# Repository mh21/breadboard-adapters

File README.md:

# breadboard-adapters

Various small schematics + PCBs for prototyping on breadboards

## TPS709xx breadboard adapter

TPS709xx breadboard adapter based on the reference design of the [TI datasheet](
http://www.ti.com/lit/ds/symlink/tps709.pdf).

2 layer board of 0.31x0.34 inches (7.77x8.66 mm). 

<a href="https://oshpark.com/shared_projects/ZPfzHzE1"></img></a>

Details: [TI datasheet](http://www.ti.com/lit/ds/symlink/tps709.pdf)

BOM:
- 1x TPS709xx voltage regulator
- 1x 3x1 pin headers
- 1x 1u 25V X7R capacitor, 0805
- 1x 2u2 10V X7R capacitor, 0805

## Breadboard level shifter

4x breadboard level shifter similar to [Sparkfun #12009](https://www.sparkfun.com/products/12009) and [Adafruit #757](https://www.adafruit.com/products/757).

2 layer board of 0.40x0.50 inches (10.21x12.75 mm)

<a href="https://oshpark.com/shared_projects/CuXsJ7my"></img></a>

Details: [NXP app note AN10441](http://www.nxp.com/documents/application_note/AN10441.pdf)

BOM:
- 2x BSS138PS, SOT-363
- 2x 5x1 pin headers
- 8x 10k resistors, 0603

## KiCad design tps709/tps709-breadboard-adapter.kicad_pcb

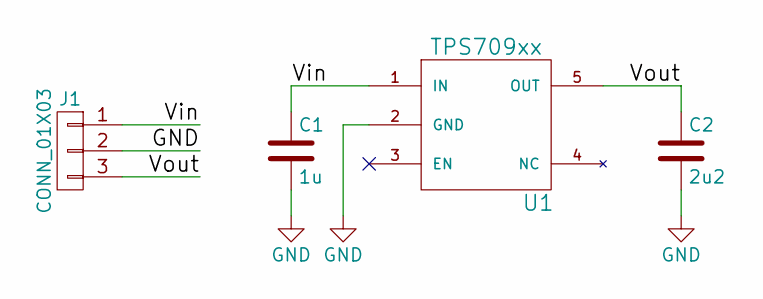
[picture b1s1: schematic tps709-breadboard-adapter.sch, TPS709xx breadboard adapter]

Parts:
C1: 1u; C_0603_HandSoldering; MPN GCM188R71E105KA64D
C2: 2u2; C_0603_HandSoldering; MPN C0603C225K8RACTU
J1: CONN_01X03; Pin_Header_Straight_1x03_Pitch2.54mm; MPN M20-9990345
U1: TPS709xx; SOT-23-5_HandSoldering; MPN TPS70918DBVT

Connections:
/Vin: C1.1, J1.1, U1.1 (IN)
/Vout: C2.1, J1.3, U1.5 (OUT)
GND: C1.2, C2.2, J1.2, U1.2 (GND)

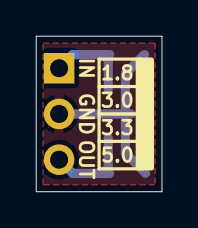
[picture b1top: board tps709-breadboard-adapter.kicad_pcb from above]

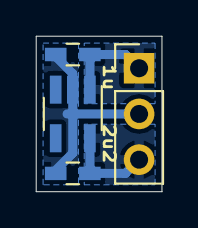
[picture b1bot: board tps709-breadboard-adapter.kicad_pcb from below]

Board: 2 copper layers, 7.0 x 8.6 mm, 4 parts (4 on the bottom side), 3 nets.

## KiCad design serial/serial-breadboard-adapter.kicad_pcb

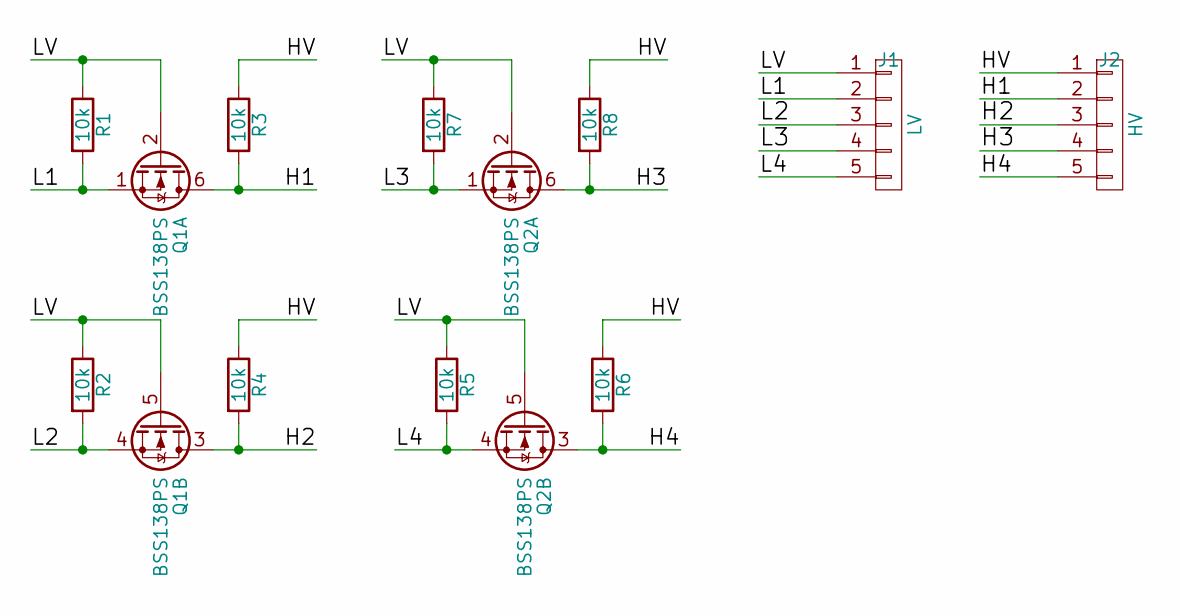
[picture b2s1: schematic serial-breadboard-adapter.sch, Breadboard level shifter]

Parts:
J1: LV; Pin_Header_Straight_1x05_Pitch2.54mm; MPN M20-9990545
J2: HV; Pin_Header_Straight_1x05_Pitch2.54mm; MPN M20-9990545
Q1, Q2: BSS138PS; SOT-363_SC-70-6_Handsoldering; MPN BSS138PS
R1, R2, R3, R4, R5, R6, R7, R8: 10k; R_0603_HandSoldering; MPN MCWR06X1002FTL

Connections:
/H1: J2.2, Q1.6 (D), R3.2
/H2: J2.3, Q1.3 (D), R4.2
/H3: J2.4, Q2.6 (D), R8.2
/H4: J2.5, Q2.3 (D), R6.2
/HV: J2.1, R3.1, R4.1, R6.1, R8.1
/L1: J1.2, Q1.1 (S), R1.2
/L2: J1.3, Q1.4 (S), R2.2
/L3: J1.4, Q2.1 (S), R7.2
/L4: J1.5, Q2.4 (S), R5.2
/LV: J1.1, Q1.2 (G), Q1.5 (G), Q2.2 (G), Q2.5 (G), R1.1, R2.1, R5.1, R7.1

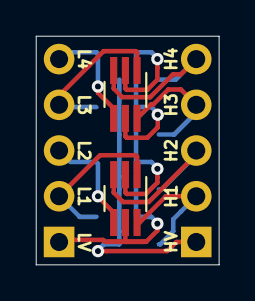
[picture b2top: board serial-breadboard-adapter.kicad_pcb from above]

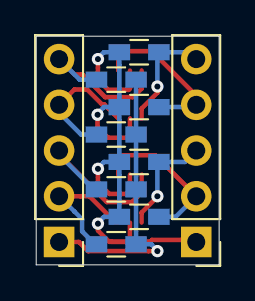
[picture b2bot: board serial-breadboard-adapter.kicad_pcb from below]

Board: 2 copper layers, 10.2 x 12.7 mm, 12 parts (10 on the bottom side), 10 nets.

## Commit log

2017-03-30 Initial commit.
2017-04-08 Change tps709 adapter to use 0603 capacitors.
